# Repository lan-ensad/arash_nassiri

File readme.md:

# Ambilight -- Arash Nassiri

Systeme ambilight temps reel : un script Python analyse les bords d'une video, extrait les couleurs dominantes et les envoie en **UDP via WiFi** a un microcontroleur Seeed XIAO ESP32-C6 qui pilote **2 chaines** de 260 LEDs WS2812 (520 LEDs au total, 8.67 m, 60 pixels/m).

L'ESP32 et l'ordinateur de diffusion sont connectes sur un **reseau WiFi ferme** dedie. L'ESP32 est monte au milieu du bas ; les 2 chaines partent de ce point central vers la gauche et la droite, pour minimiser la longueur du fil data.

## Architecture

```
Source video (fichier ou capture HDMI via Cam Link)
    │
    ▼
Script Python (PC)  ──►  analyse des bords  ──►  traitement couleur  ──►  UDP (WiFi)
                         (zones.py)               (colors.py)             (udp_sender.py)
                                                                               │
                                                                               ▼
                                                                 Reseau WiFi ferme
                                                                               │
                                                                               ▼
                                                                      Firmware ESP32-C6
                                                                      (NeoPixelBus → WS2812)
                                                                               │
                                                                               ▼
                                                                      2 chaines de 260 LEDs
                                                                      (A = gauche, B = droite)
```

## Disposition physique

Vu depuis la position du spectateur, **face a l'ecran** :

```
         ┌─────────────────────────────────────────────────────┐
         │                     (haut : pas de ruban)           │
         │                                                     │
         │                                                     │
      ▲  │                                                     │  ▲
      │  │                                                     │  │
  150 │  │                                                     │  │ 150
  LEDs│  │                    [  E C R A N  ]                  │  │ LEDs
      │  │                                                     │  │
      │  │                                                     │  │
      │  └──────────┐                              ┌───────────┘  │
      │             │                              │              │
      └─ CHAINE A ──┤                              ├── CHAINE B ──┘
     (cote gauche)  │                              │   (cote droit)
                    │       ┌──────────────┐       │
      ◄─────────────┤       │  ESP32 + PCB │       ├─────────────►
       110 LEDs     └───────┤              ├───────┘    110 LEDs
       demi-bas             │    milieu    │            demi-bas
       gauche               └──────┬───────┘             droit
                                   │
                                   ▼
                            Alimentation 5 V
```

- **Chaine A** (260 LEDs) : cote **GAUCHE** du spectateur + demi-bas gauche
- **Chaine B** (260 LEDs) : cote **DROIT** du spectateur + demi-bas droit

Pour chaque chaine, le flux data part de l'ESP32, remonte le demi-bas (110 LEDs) puis le cote vertical (150 LEDs, du bas vers le haut).

## Chiffres cles

- **520 LEDs** WS2812 (2 chaines de 260, densite 60 px/m)
- **Alimentation** Mean Well LRS150F-5 (5 V / 30 A)
- **ESP32-C6** sortie D9 = chaine A (gauche), D10 = chaine B (droite)
- **Level shifter** SN74HCT14N (3.3 V → 5 V) entre ESP32 et rubans
- **Protocole** UDP port 4210, 2 paquets/frame (785 o chacun), ~47 KB/s a 30 fps

## Structure du projet

```
arash_nassiri/
├── readme.md               Ce fichier -- documentation generale
│
├── Firmware/               Firmware ESP32-C6 (PlatformIO)
│   └── README.md           → Installation, flashage, protocole UDP, troubleshooting firmware
│
├── script/                 Script Python (cote ordinateur)
│   └── README.md           → Installation, configuration, utilisation, troubleshooting soft
│
├── kicad/                  Electronique (schema + BOM + cablage)
│   ├── README.md           → Dimensionnement, BOM, cablage, precautions electriques
│   └── ambilight_kicad/    Projet KiCad
│
├── test_videos/            Videos de test (generees par ffmpeg)
├── run.sh                  Lancement production (fullscreen + unclutter)
└── _devis/                 Documents administratifs (devis, factures)
```

## Documentation par composant

| Composant | Documentation | Concerne |
|---|---|---|
| Electronique | [kicad/README.md](kicad/README.md) | Dimensionnement, BOM, cablage, SN74HCT14N, alimentation |
| Firmware ESP32 | [Firmware/README.md](Firmware/README.md) | PlatformIO, WiFi, flashage, protocole UDP |
| Script Python | [script/README.md](script/README.md) | OpenCV, source video, pipeline couleur, parametres |

## Demarrage rapide

Ordre recommande pour une premiere mise en route :

1. **Electronique** : lire [kicad/README.md](kicad/README.md), fabriquer / cabler la partie power + level shifter + rubans
2. **Firmware** : remplir `Firmware/src/wifi_config.h` puis flasher (voir [Firmware/README.md](Firmware/README.md))
3. **Script Python** : installer le venv et configurer `script/config.py` (voir [script/README.md](script/README.md))
4. **Lancer** : `./run.sh` depuis la racine (ou configurer le service systemd, section suivante)

Pour **tester le pipeline Python sans materiel** (loopback UDP) : voir la section Troubleshooting dans [script/README.md](script/README.md).

## Lancement automatique au boot (service systemd user)

Pour une installation permanente. Recommande quand la source video est externe (Cam Link) et `headless = True` dans `script/config.py` -- aucune session graphique requise.

`run.sh` integre deja l'attente reseau (ping de la passerelle par defaut, max 30 s) et une rotation simple des logs au demarrage : aucune modification requise avant installation.

### Prerequis a verifier dans `script/config.py`

| Parametre | Valeur recommandee | Raison |
|---|---|---|
| `headless` | `True` | Pas de session graphique sous systemd user (sauf si `DISPLAY` configure dans l'unit) |
| `terminal_preview` | `False` | Pas de terminal → les codes ANSI du preview polluent le fichier de log |
| `dry_run` | `False` | Sinon aucun paquet UDP n'est envoye |
| `video_path` / `camera_index` | source reelle | `video_path` est resolu relativement a `script/` |

IP ESP32 coherente entre `script/config.py` (`esp32_ip`) et `Firmware/src/wifi_config.h` (`LOCAL_IP_BYTES`).

### 1. Creer le service

Fichier `~/.config/systemd/user/ambilight.service` :

```ini
[Unit]
Description=Ambilight video capture and UDP send
After=network-online.target
Wants=network-online.target

[Service]
Type=simple
WorkingDirectory=/path/to/arash_nassiri
ExecStart=/path/to/arash_nassiri/run.sh
Restart=on-failure
RestartSec=5
Environment=PYTHONUNBUFFERED=1

# Double destination des logs :
#  - Fichier persistant (rotation geree par run.sh au demarrage, >10 Mo → archive timestampee, max 5 backups)
#  - Journal systemd user natif (rotation + compression gerees par journald)
StandardOutput=append:/path/to/arash_nassiri/logs/ambilight.log
StandardError=append:/path/to/arash_nassiri/logs/ambilight.log

[Install]
WantedBy=default.target
```

> Adapter les 3 chemins `/path/to/arash_nassiri/...` au chemin reel du projet. Le dossier `logs/` est cree automatiquement par `run.sh`.

### 2. Activer et demarrer

```bash
mkdir -p ~/.config/systemd/user
# (copier ambilight.service dans ce dossier)
systemctl --user daemon-reload
systemctl --user enable --now ambilight.service
```

### 3. Permettre le demarrage sans login utilisateur (lingering)

```bash
sudo loginctl enable-linger $USER
```

Sans cette ligne, le service ne demarre qu'apres connexion interactive.

### 4. Prerequis systeme

Utilisateur dans le groupe `video` pour acceder a la capture (Cam Link, webcam) :

```bash
sudo usermod -aG video $USER
# logout/login pour que le groupe prenne effet
```

### 5. Operer

```bash
# Etat
systemctl --user status ambilight.service

# Logs temps reel -- deux options equivalentes
tail -f logs/ambilight.log                          # fichier dedie
journalctl --user -u ambilight.service -f           # journal systemd

# Logs filtres
journalctl --user -u ambilight.service -p err       # erreurs uniquement
journalctl --user -u ambilight.service --since "1 hour ago"

# Cycle de vie
systemctl --user restart ambilight.service
systemctl --user stop    ambilight.service
```

### 6. Desinstaller le service

```bash
systemctl --user disable --now ambilight.service
rm -f ~/.config/systemd/user/ambilight.service
systemctl --user daemon-reload
sudo loginctl disable-linger $USER   # optionnel
```

## Reseau WiFi ferme

PC et ESP32 sur un reseau WiFi dedie (routeur/AP dedie ou hotspot du PC). Aucun trafic Internet ni autre appareil -- isolation garantit :
- Latence predictible (pas de contention)
- IP statique possible pour l'ESP32

**Config par defaut** :

| Parametre | Valeur | Fichier |
|---|---|---|
| IP ESP32 | `<IP_ESP>` | `script/config.py` + `Firmware/src/wifi_config.h` |
| Hostname ESP32 | `esp_ambilight` | `Firmware/src/wifi_config.h` |
| Port UDP | `4210` | `Firmware/src/wifi_config.h` |
| SSID / password | <SSID + PASS\> | `Firmware/src/wifi_config.h` |

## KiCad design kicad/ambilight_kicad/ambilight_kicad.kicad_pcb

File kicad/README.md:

# Electronique -- Ambilight

Ce dossier contient le schema KiCad et toute la documentation electronique du projet (matiere, cablage, calculs, precautions).

Pour la partie logicielle (script Python + firmware ESP32) voir le [readme.md](../readme.md) a la racine.

## Vue d'ensemble

```
                                Mean Well LRS150F-5
                               ┌──────────────────┐
                       AC IN ──┤ L   N   ⏚        │
                               │                  │
                               │   +5V    GND     │
                               └───┬───────┬──────┘
                                   │       │
                              1000uF cap   │
                                   │       │
          ┌────────────────────────┼───────┼────────────────────────┐
          │  RAIL 5V (16AWG)       │       │  RAIL GND (16AWG)      │
          │                        │       │                        │
          │    ┌───────────────────┼───────┼──────────┐             │
          ▼    ▼                   ▼       ▼          ▼             ▼
     INJECTION 1              INJECTION 2        INJECTION 3
    (extremite gauche,        (milieu du bas,    (extremite droite,
     en haut du cote)         pres de l'ESP)     en haut du cote)
      100uF cap                100uF cap          100uF cap

    ┌─────────────────────────────────┬─────────────────────────────────┐
    │          CHAINE A (260 LEDs)    │          CHAINE B (260 LEDs)    │
    │  ┌────────────┬────────────┐    │    ┌────────────┬────────────┐  │
    │  │  GAUCHE    │  1/2 BAS   │    │    │  1/2 BAS   │  DROITE    │  │
    │  │  (150)     │  gauche    │    │    │  droite    │  (150)     │  │
    │  │  bas→haut  │  (110)     │    │    │  (110)     │  bas→haut  │  │
    │  │            │  gauche ←  │◄DIN│DIN►│  → droite  │            │  │
    │  │   DOUT ←── │ ← ─────────│    │    │────────── →│ ──► DOUT   │  │
    │  └────────────┴────────────┘    │    └────────────┴────────────┘  │
    └─────────────────────────────────┴─────────────────────────────────┘
                                 ▲       ▲
                    330 ohm ─────┤       ├──── 330 ohm
                                 │       │
                         data 5V │       │ data 5V (< 30 cm, 22AWG)
                          pin 4  │       │ pin 10
                    ┌────────────┴───────┴─────────────┐
                    │  SN74HCT14N (hex Schmitt inv.)   │
                    │                                  │
                    │  Chaine A : pin 1 → pin 2,       │
                    │             pin 3 → pin 4        │
                    │  Chaine B : pin 13 → pin 12,     │
                    │             pin 11 → pin 10      │
                    │                                  │
                    │  VCC = pin 14 (+5V) + 100nF      │
                    │  GND = pin 7                     │
                    │  entrees NC (5, 9) → GND         │
                    └──────▲──────────────▲────────────┘
                           │ pin 1        │ pin 13
                           │ data A 3.3V  │ data B 3.3V
                    ┌──────┴──────────────┴────────────┐
                    │  XIAO ESP32-C6                   │
                    │     D9 ─(chaine A gauche)        │
                    │    D10 ─(chaine B droite)        │
                    │    USB ← 5V (alim seule,         │
                    │          chargeur ou powerbank)  │
                    │    WiFi ◄─── UDP (port 4210)     │
                    └─────────────────────▲────────────┘
                                          │ reseau WiFi ferme dedie
                                          │
                                   ┌──────┴───────┐
                                   │  PC (Python) │
                                   │  udp_sender  │
                                   └──────────────┘
```

## Dimensionnement

### Installation

| Cote | Longueur |
|---|---|
| Bas | 368 cm |
| Droite | 250 cm |
| Gauche | 250 cm |
| **Total** | **868 cm = 8.68 m** |

### LEDs

Densite du ruban : **60 pixels/m**

| Cote | Longueur | LEDs |
|---|---|---|
| Bas | 3.67 m | 3.67 x 60 = **220** (110 + 110, symetrique) |
| Droite | 2.50 m | 2.50 x 60 = **150** |
| Gauche | 2.50 m | 2.50 x 60 = **150** |
| **Total** | **8.67 m** | **520 LEDs** |

Le bas est ramene de 221 a **220 LEDs** pour une **repartition symetrique** (110 par demi-cote). Le gain physique est de 1,67 cm, negligeable visuellement.

### Repartition en 2 chaines

L'ESP32 est positionne au **milieu du bas**. Deux chaines de LEDs partent de ce point central vers l'exterieur, pilotees chacune par un GPIO different :

| Chaine | GPIO | Trajet | LEDs |
|---|---|---|---|
| **A** (gauche) | D9 | demi-bas milieu → gauche, puis cote gauche bas → haut | 110 + 150 = **260** |
| **B** (droite) | D10 | demi-bas milieu → droite, puis cote droit bas → haut | 110 + 150 = **260** |

Avantages vs une seule chaine de 521 LEDs :
- Fil data 10 fois plus court (< 30 cm au lieu de ~1,85 m vers un coin)
- Rafraichissement LED plus rapide (2 chaines en parallele, ~260 LEDs chacune au lieu de 521)
- Ligne data moins sensible aux perturbations

### Puissance

Chaque LED WS2812 consomme au maximum 60 mA a 5 V (20 mA par canal R, G, B a pleine intensite).

| Scenario | Courant par LED | Courant total | Puissance (5 V) |
|---|---|---|---|
| Maximum (blanc 100%) | 60 mA | 520 x 60 mA = **31.2 A** | **156.0 W** |
| Utilisation typique ambilight (~30%) | ~20 mA | 520 x 20 mA = **10.4 A** | **52.0 W** |

**Alimentation choisie** : 1x Mean Well LRS150F-5 -- 5 V / 30 A (150 W).

> 30 A couvre le maximum theorique (31.2 A) a ~96%. En pratique l'ambilight ne
> depasse jamais le blanc pur simultane sur toutes les LEDs ; le budget typique
> (~10 A) laisse une large marge. Si un contenu pousse ponctuellement au-dela,
> la LRS150F-5 tolere des pics courts a 110% (33 A).

## Cablage de l'ESP32-C6

| Broche ESP32-C6 | Connexion | Note |
|---|---|---|
| USB-C ou pad 5V | 5 V depuis la PSU via Wago ou regulateur | Alim seule — les donnees passent par WiFi |
| D9 | Level shifter IN chaine A (pin 1) | Signal data chaine A (gauche, 260 LEDs) |
| D10 | Level shifter IN chaine B (pin 13) | Signal data chaine B (droite, 260 LEDs) |
| GND | GND commun (PSU + level shifter) | **Obligatoire** |
| WiFi (integre) | Reseau ferme dedie | Reception UDP du PC |

> **Decouplage ESP32** : placer 22 uF electrolytique + 100 nF ceramique en parallele sur le rail 5 V au plus pres du VBUS, pour filtrer le bruit HF genere par les 520 LEDs qui commutent a 800 kHz.

## Cablage du level shifter SN74HCT14N

Boitier DIP-14 (6 inverseurs Schmitt trigger independants). On utilise **4 portes** (2 cascades de 2 inverseurs), une cascade par chaine. 2 portes restent inutilisees.

```
           ┌───U───┐
    1A  ──1┤       ├14──  VCC (+5 V)
    1Y  ──2┤       ├13──  6A  ← D10 (chaine B, 3.3V)
    2A  ──3┤       ├12──  6Y
    2Y  ──4┤       ├11──  5A
    3A  ──5┤       ├10──  5Y  → 330 ohm → chaine B DIN (5V)
    3Y  ──6┤       ├9──── 4A  (NC → GND)
    GND ──7┤       ├8──── 4Y  (NC)
           └───────┘
```

### Chaine A (gauche) -- cascade inverseurs 1 et 2

| Broche | Role | Connexion |
|---|---|---|
| 1 (1A) | Entree inverseur 1 | Signal 3.3 V depuis ESP32 **D9** |
| 2 (1Y) | Sortie inverseur 1 | Relier a la broche 3 |
| 3 (2A) | Entree inverseur 2 | Relier a la broche 2 |
| 4 (2Y) | Sortie inverseur 2 (5 V) | Resistance 330 ohm puis DIN chaine A |

### Chaine B (droite) -- cascade inverseurs 6 et 5

| Broche | Role | Connexion |
|---|---|---|
| 13 (6A) | Entree inverseur 6 | Signal 3.3 V depuis ESP32 **D10** |
| 12 (6Y) | Sortie inverseur 6 | Relier a la broche 11 |
| 11 (5A) | Entree inverseur 5 | Relier a la broche 12 |
| 10 (5Y) | Sortie inverseur 5 (5 V) | Resistance 330 ohm puis DIN chaine B |

### Portes inutilisees (inverseurs 3 et 4)

| Broche | Role | Connexion |
|---|---|---|
| 5 (3A), 9 (4A) | Entrees inutilisees | **Obligatoire : relier a GND** |
| 6 (3Y), 8 (4Y) | Sorties inutilisees | Laisser en l'air |

### Alimentation

| Broche | Connexion |
|---|---|
| 14 (VCC) | +5 V depuis la PSU |
| 7 (GND) | GND commun avec PSU et ESP32 |

**Decouplage** : condensateur 100 nF ceramique (marquage "104") entre broche 14 et broche 7, **au plus pres du chip** (pattes < 5 mm).

## Fichiers KiCad

Le projet KiCad complet est dans [ambilight_kicad/](ambilight_kicad/).

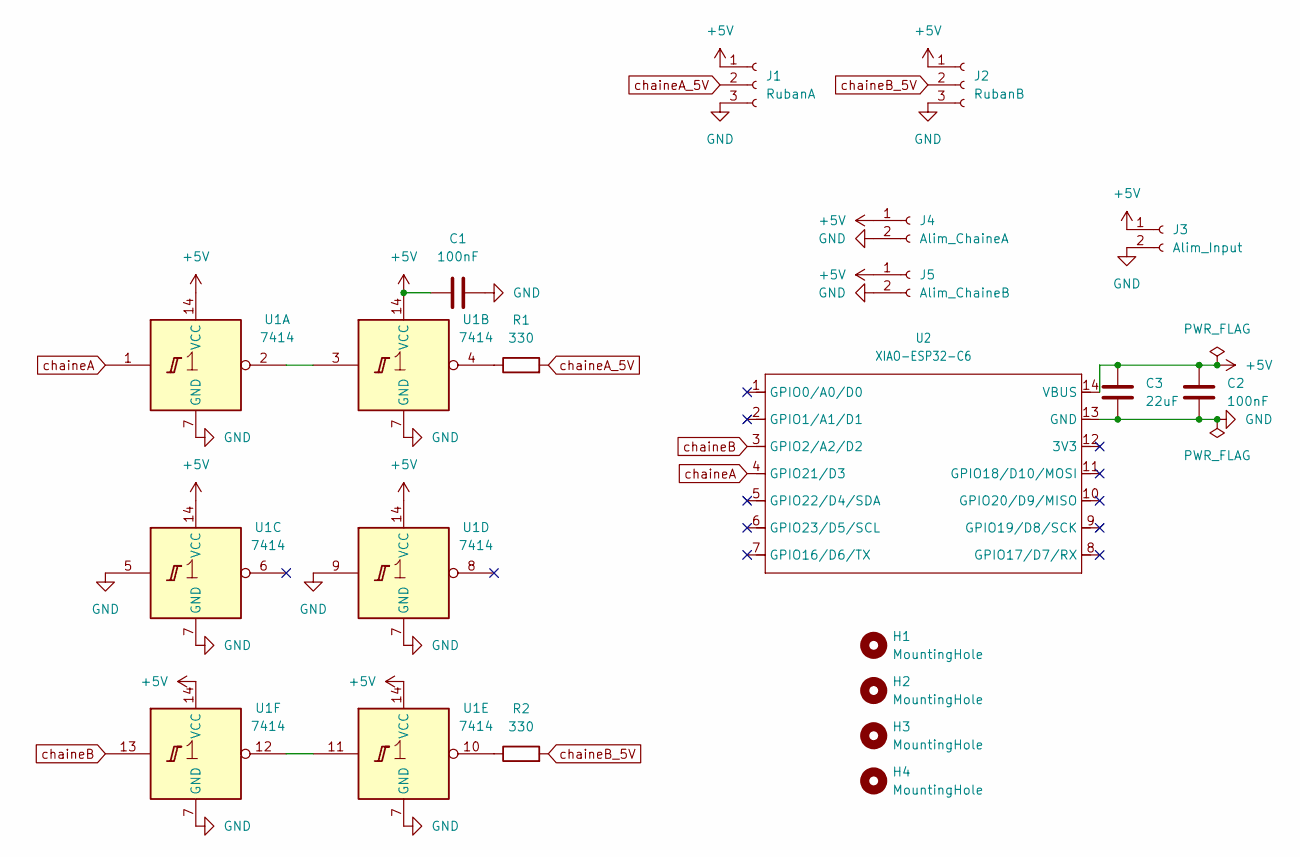
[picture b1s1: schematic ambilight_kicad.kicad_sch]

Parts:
C1, C2: 100nF; C_Disc_D3.8mm_W2.6mm_P2.50mm
C3: 22uF; C_Radial_D6.3mm_H7.0mm_P2.50mm
H1, H2, H3, H4: MountingHole; MountingHole_3.2mm_M3
J1: RubanA; TerminalBlock_Phoenix_MKDS-1,5-3-5.08_1x03_P5.08mm_Horizont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
J2: RubanB; TerminalBlock_Phoenix_MKDS-1,5-3-5.08_1x03_P5.08mm_Horizont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
J3: Alim_Input; TerminalBlock_Phoenix_MKDS-1,5-2-5.08_1x02_P5.08mm_Horizont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
J4: Alim_ChaineA; TerminalBlock_Phoenix_MKDS-1,5-2-5.08_1x02_P5.08mm_Horizont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
J5: Alim_ChaineB; TerminalBlock_Phoenix_MKDS-1,5-2-5.08_1x02_P5.08mm_Horizont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
R1, R2: 330; R_Axial_DIN0207_L6.3mm_D2.5mm_P7.62mm_Horizontal
U1: 7414; DIP-14_W7.62mm
U2: XIAO-ESP32-C6; XIAO-ESP32C6-DIP

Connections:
+5V: C1.1, C2.1, C3.1, J1.1, J2.1, J3.1, J4.1, J5.1, U1.14 (VCC), U2.14 (VBUS)
GND: C1.2, C2.2, C3.2, J1.3, J2.3, J3.2, J4.2, J5.2, U1.5, U1.7 (GND), U1.9, U2.13 (GND)
unnamed: R1.1, U1.4
unnamed: R2.1, U1.10
unnamed: U1.2, U1.3
unnamed: U1.11, U1.12
chaineA: U1.1, U2.4 (GPIO21/D3)
chaineA_5V: J1.2, R1.2
chaineB: U1.13, U2.3 (GPIO2/A2/D2)
chaineB_5V: J2.2, R2.2

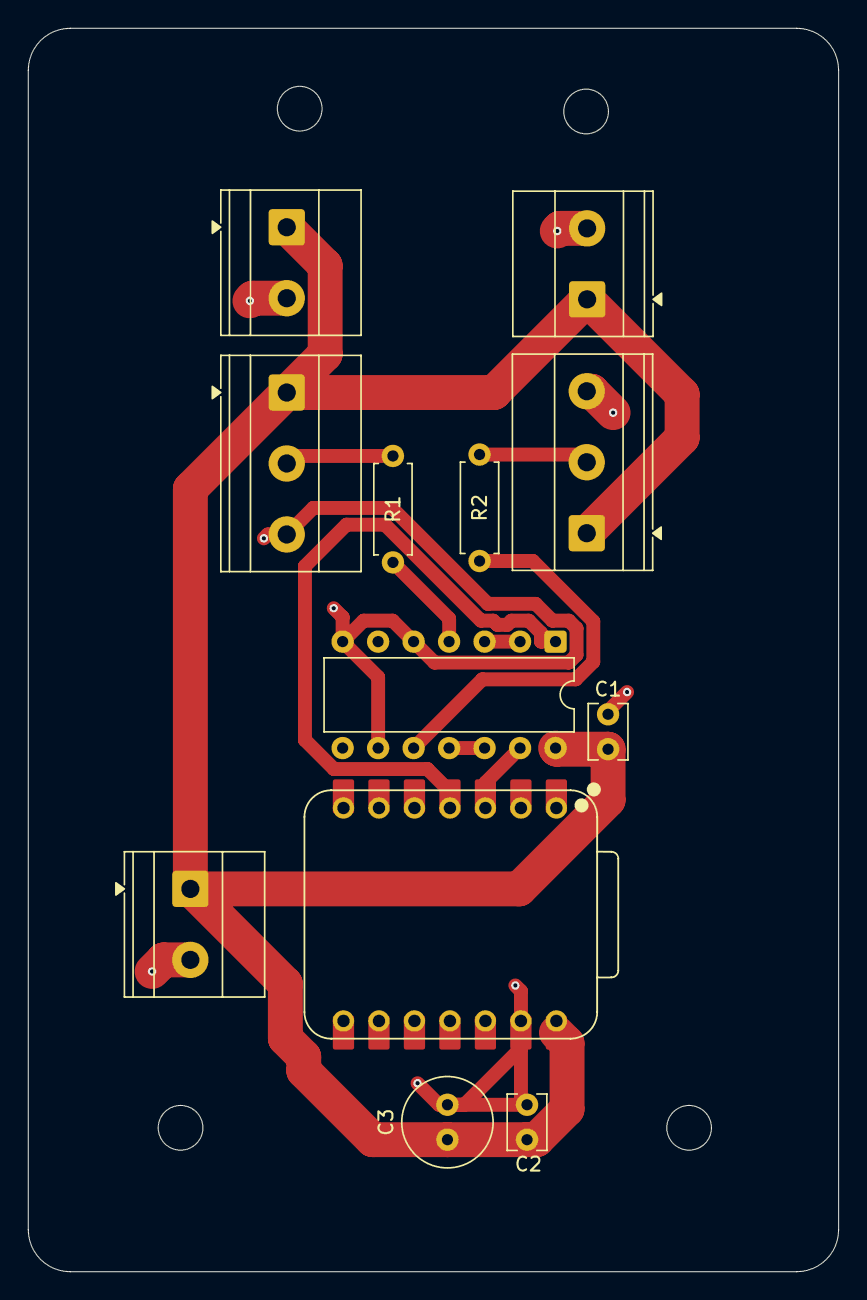
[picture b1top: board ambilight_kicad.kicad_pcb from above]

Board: 2 copper layers, 58.0 x 89.0 mm, 16 parts (0 on the bottom side), 10 nets.

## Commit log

2026-04-23 rm update
2026-04-25 fix zones blend
2026-05-05 new-branch-osc
